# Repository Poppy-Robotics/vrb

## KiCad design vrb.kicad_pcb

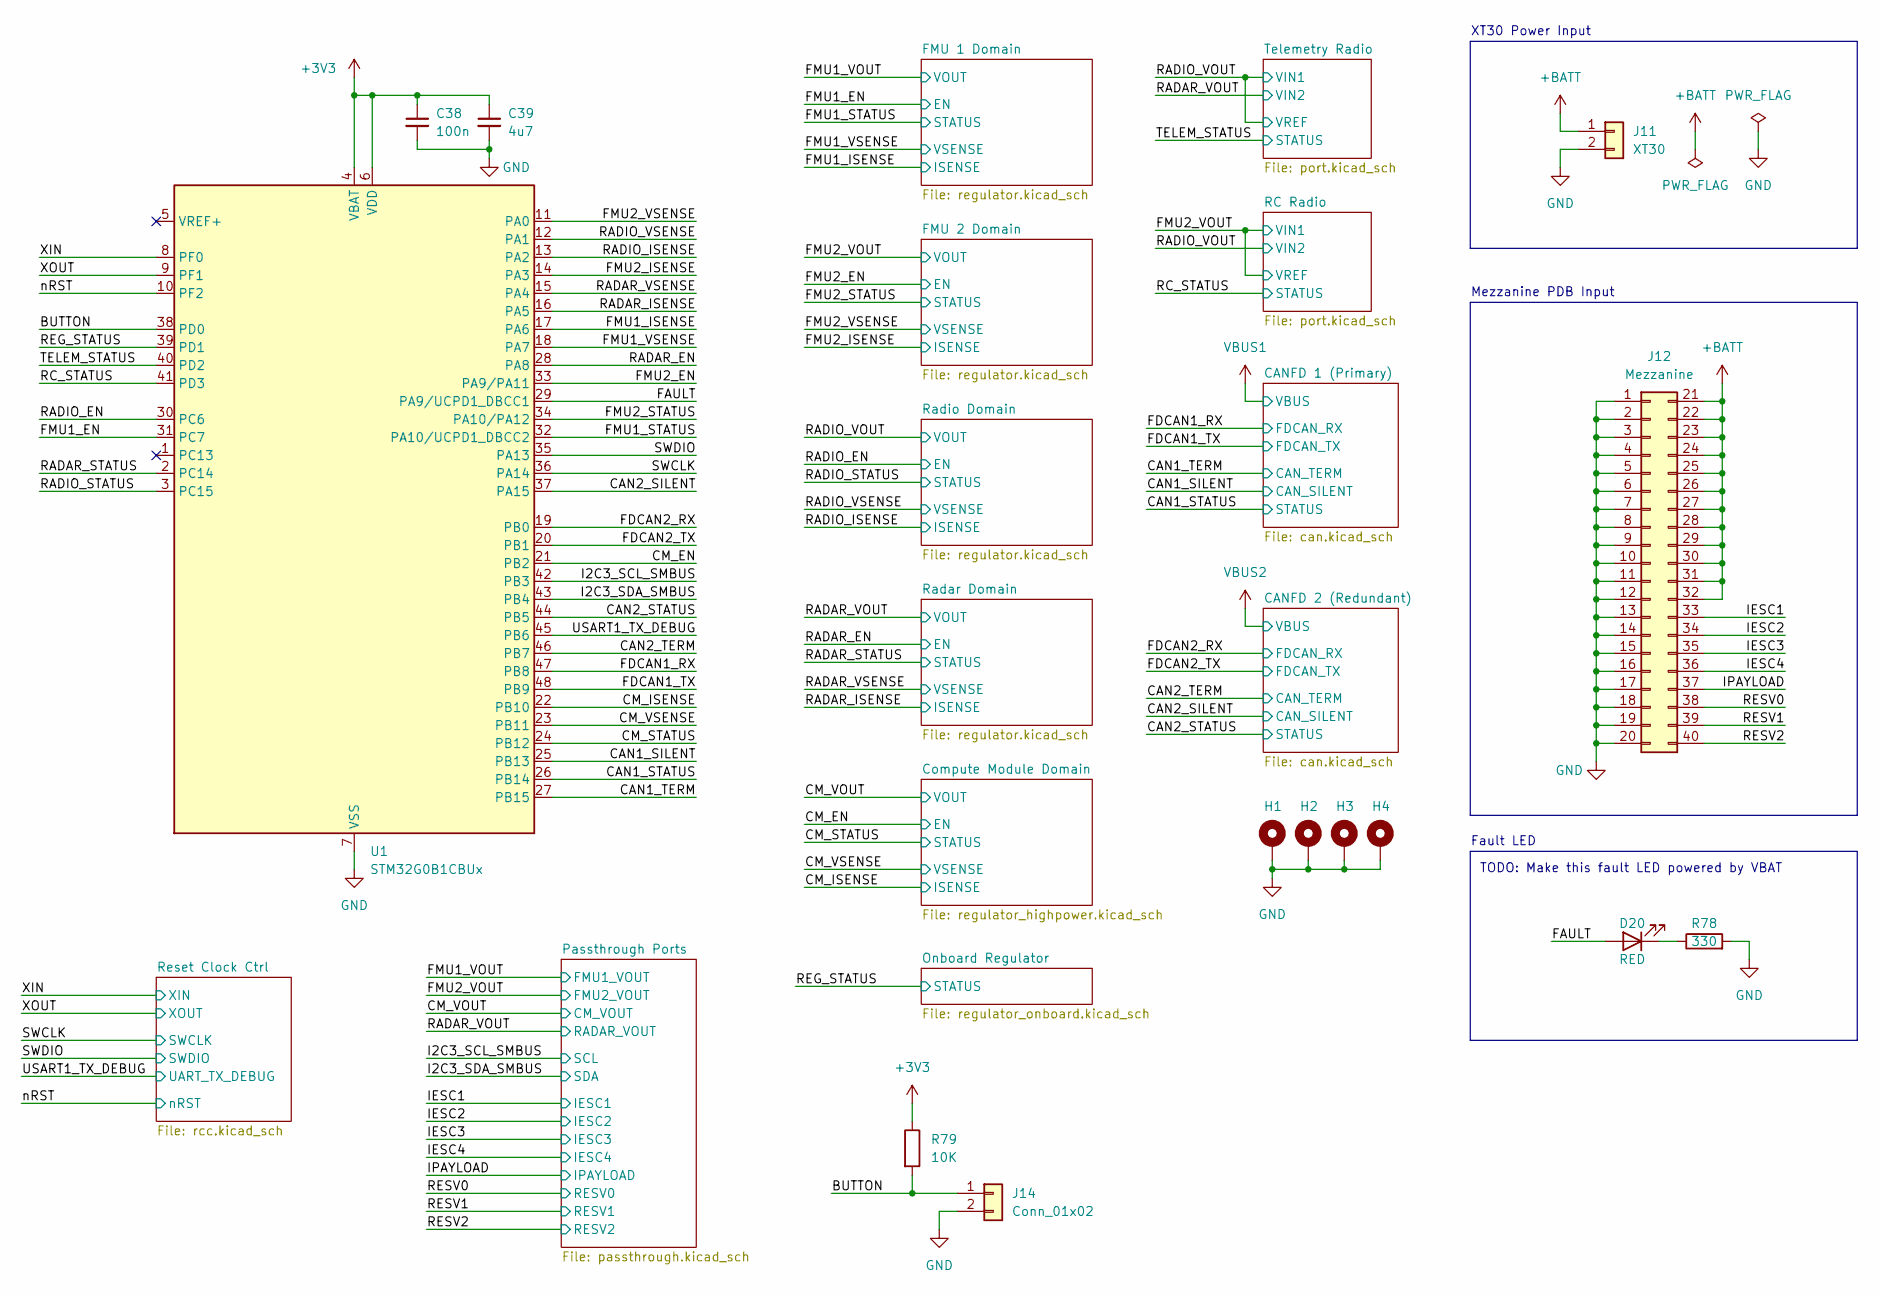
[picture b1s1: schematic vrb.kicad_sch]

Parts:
C38: 100n; C_0402_1005Metric
C39: 4u7; C_0402_1005Metric
D20: RED; LED_0603_1608Metric
H1, H2, H3, H4: MountingHole_Pad; MountingHole_3.2mm_M3_Pad_Via
J11: XT30; AMASS_XT30PW-M_1x02_P2.50mm_Horizontal
J12: Mezzanine; CON_528850474_MOL
J14: Conn_01x02; PinHeader_1x02_P2.54mm_Vertical
R78: 330; R_0402_1005Metric
R79: 10K; R_0402_1005Metric
U1: STM32G0B1CBUx; QFN-48-1EP_7x7mm_P0.5mm_EP5.6x5.6mm

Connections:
+BATT: J11.1, J12.21, J12.22, J12.23, J12.24, J12.25, J12.26, J12.27, J12.28, J12.29, J12.30, J12.31, J12.32; also elsewhere on the board
/BUTTON: J14.1, R79.2, U1.38 (PD0)
/CAN1_SILENT: U1.25 (PB13); also elsewhere on the board
/CAN1_STATUS: U1.26 (PB14); also elsewhere on the board
/CAN1_TERM: U1.27 (PB15); also elsewhere on the board
/CAN2_SILENT: U1.37 (PA15); also elsewhere on the board
/CAN2_STATUS: U1.44 (PB5); also elsewhere on the board
/CAN2_TERM: U1.46 (PB7); also elsewhere on the board
/CM_EN: U1.21 (PB2); also elsewhere on the board
/CM_ISENSE: U1.22 (PB10); also elsewhere on the board
/CM_STATUS: U1.24 (PB12); also elsewhere on the board
/CM_VSENSE: U1.23 (PB11); also elsewhere on the board
/FAULT: D20.2 (A), U1.29 (PA9/UCPD1_DBCC1)
/FDCAN1_RX: U1.47 (PB8); also elsewhere on the board
/FDCAN1_TX: U1.48 (PB9); also elsewhere on the board
/FDCAN2_RX: U1.19 (PB0); also elsewhere on the board
/FDCAN2_TX: U1.20 (PB1); also elsewhere on the board
/FMU1_EN: U1.31 (PC7); also elsewhere on the board
/FMU1_ISENSE: U1.17 (PA6); also elsewhere on the board
/FMU1_STATUS: U1.32 (PA10/UCPD1_DBCC2); also elsewhere on the board
/FMU1_VSENSE: U1.18 (PA7); also elsewhere on the board
/FMU2_EN: U1.33 (PA9/PA11); also elsewhere on the board
/FMU2_ISENSE: U1.14 (PA3); also elsewhere on the board
/FMU2_STATUS: U1.34 (PA10/PA12); also elsewhere on the board
/FMU2_VSENSE: U1.11 (PA0); also elsewhere on the board
/I2C3_SCL_SMBUS: U1.42 (PB3); also elsewhere on the board
/I2C3_SDA_SMBUS: U1.43 (PB4); also elsewhere on the board
/IESC1: J12.33; also elsewhere on the board
/IESC2: J12.34; also elsewhere on the board
/IESC3: J12.35; also elsewhere on the board
/IESC4: J12.36; also elsewhere on the board
/IPAYLOAD: J12.37; also elsewhere on the board
/RADAR_EN: U1.28 (PA8); also elsewhere on the board
/RADAR_ISENSE: U1.16 (PA5); also elsewhere on the board
/RADAR_STATUS: U1.2 (PC14); also elsewhere on the board
/RADAR_VSENSE: U1.15 (PA4); also elsewhere on the board
/RADIO_EN: U1.30 (PC6); also elsewhere on the board
/RADIO_ISENSE: U1.13 (PA2); also elsewhere on the board
/RADIO_STATUS: U1.3 (PC15); also elsewhere on the board
/RADIO_VSENSE: U1.12 (PA1); also elsewhere on the board
/RC_STATUS: U1.41 (PD3); also elsewhere on the board
/REG_STATUS: U1.39 (PD1); also elsewhere on the board
/RESV0: J12.38; also elsewhere on the board
/RESV1: J12.39; also elsewhere on the board
/RESV2: J12.40; also elsewhere on the board
/SWCLK: U1.36 (PA14); also elsewhere on the board
/SWDIO: U1.35 (PA13); also elsewhere on the board
/TELEM_STATUS: U1.40 (PD2); also elsewhere on the board
/USART1_TX_DEBUG: U1.45 (PB6); also elsewhere on the board
/XIN: U1.8 (PF0); also elsewhere on the board
/XOUT: U1.9 (PF1); also elsewhere on the board
/nRST: U1.10 (PF2); also elsewhere on the board
unnamed: D20.1 (K), R78.1

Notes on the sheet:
TODO: Make this fault LED powered by VBAT
Fault LED
XT30 Power Input
Mezzanine PDB Input

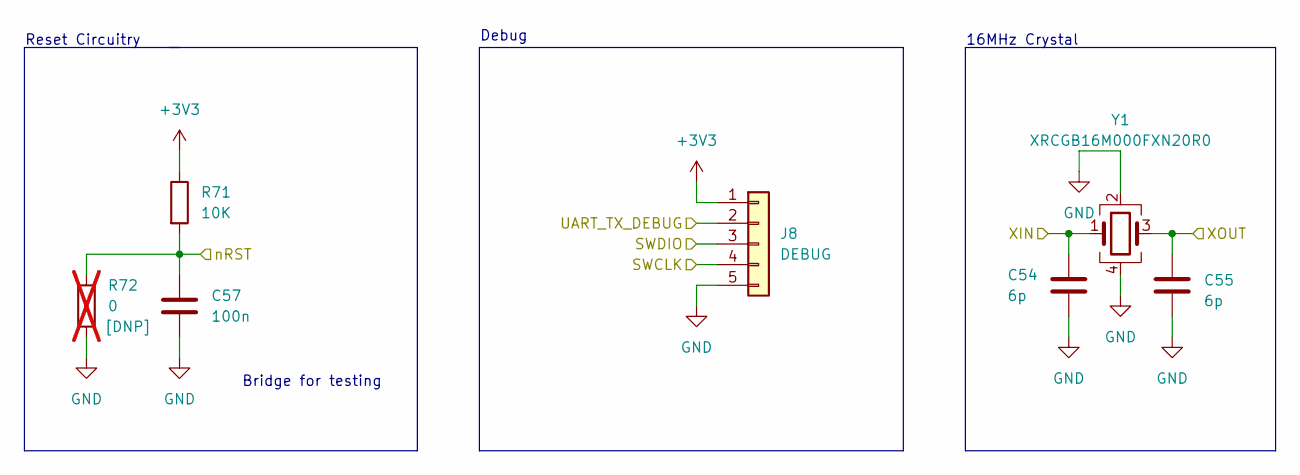
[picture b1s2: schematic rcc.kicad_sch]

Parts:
C54, C55: 6p; C_0402_1005Metric; LCSC C466231
C57: 100n; C_0402_1005Metric; LCSC C907967
J8: DEBUG; PinHeader_1x05_P2.54mm_Vertical
R71: 10K; R_0402_1005Metric; LCSC C102690
R72: 0; R_0402_1005Metric; not fitted
Y1: XRCGB16M000FXN20R0; Crystal_SMD_2016-4Pin_2.0x1.6mm; Part XRCGB16M000FXN20R0; LCSC C907977

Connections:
/SWCLK: J8.4; also elsewhere on the board
/SWDIO: J8.3; also elsewhere on the board
/USART1_TX_DEBUG: J8.2; also elsewhere on the board
/XIN: C54.1, Y1.1; also elsewhere on the board
/XOUT: C55.1, Y1.3; also elsewhere on the board
/nRST: C57.1, R71.2, R72.1; also elsewhere on the board

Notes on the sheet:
Reset Circuitry
Bridge for testing
16MHz Crystal
Debug

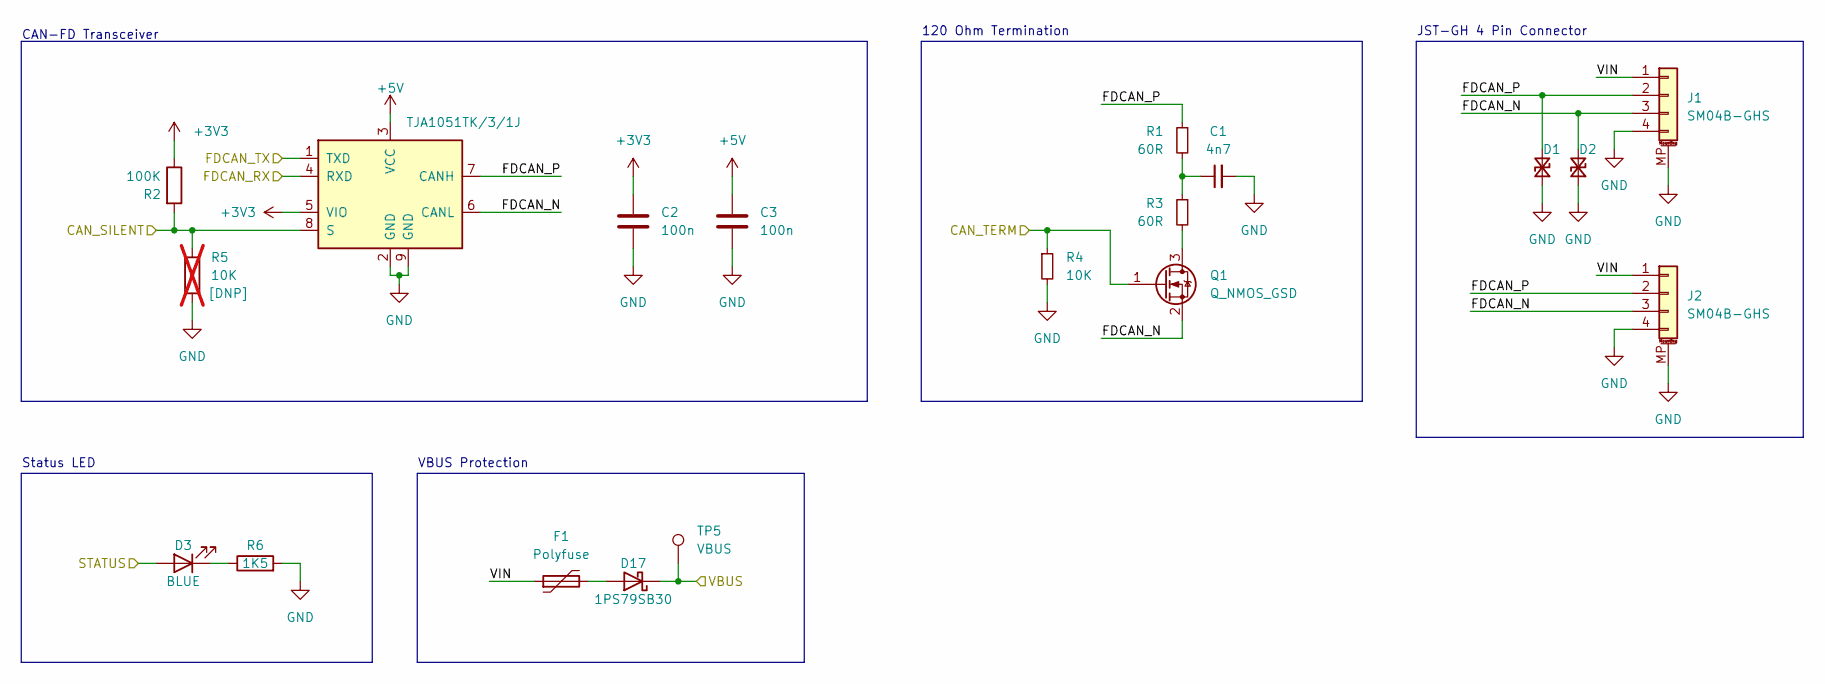
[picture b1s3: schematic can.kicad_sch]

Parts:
C1: 4n7; C_0402_1005Metric
C2, C3: 100n; C_0402_1005Metric
D1, D2: D_TVS_Small; Nexperia_DSN0603-2_0.6x0.3mm_P0.4mm
D3: BLUE; LED_0603_1608Metric
D17: 1PS79SB30; D_SOD-523; LCSC C426690
F1: Polyfuse; Fuse_1206_3216Metric
J1, J2: SM04B-GHS; JST_GH_SM04B-GHS-TB_1x04-1MP_P1.25mm_Horizontal
Q1: Q_NMOS_GSD; SOT-23-3
R1, R3: 60R; R_0402_1005Metric
R2: 100K; R_0402_1005Metric
R4: 10K; R_0402_1005Metric
R5: 10K; R_0402_1005Metric; not fitted
R6: 1K5; R_0402_1005Metric
TP5: VBUS; TestPoint_Pad_1.0x1.0mm
U2: TJA1051TK/3/1J; DFN-8-1EP_3x3mm_P0.65mm_EP1.55x2.4mm

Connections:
/CAN2_SILENT: R2.2, R5.1, U2.8 (S); also elsewhere on the board
/CAN2_STATUS: D3.2 (A); also elsewhere on the board
/CAN2_TERM: Q1.1 (G), R4.1; also elsewhere on the board
/CANFD 2 (Redundant)/FDCAN_N: D2.2 (A2), J1.3, J2.3, Q1.2 (S), U2.6 (CANL)
/CANFD 2 (Redundant)/FDCAN_P: D1.2 (A2), J1.2, J2.2, R1.1, U2.7 (CANH)
/CANFD 2 (Redundant)/VIN: F1.1, J1.1, J2.1
/FDCAN2_RX: U2.4 (RXD); also elsewhere on the board
/FDCAN2_TX: U2.1 (TXD); also elsewhere on the board
unnamed: C1.1, R1.2, R3.1
unnamed: D3.1 (K), R6.1
unnamed: D17.2 (A), F1.2
unnamed: Q1.3 (D), R3.2
VBUS2: D17.1 (K), TP5.1; also elsewhere on the board

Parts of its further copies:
C24: 4n7; C_0402_1005Metric
C25, C26: 100n; C_0402_1005Metric
D8, D9: D_TVS_Small; Nexperia_DSN0603-2_0.6x0.3mm_P0.4mm
D10: BLUE; LED_0603_1608Metric
D19: 1PS79SB30; D_SOD-523; LCSC C426690
F6: Polyfuse; Fuse_1206_3216Metric
J7, J9: SM04B-GHS; JST_GH_SM04B-GHS-TB_1x04-1MP_P1.25mm_Horizontal
Q2: Q_NMOS_GSD; SOT-23-3
R39, R41: 60R; R_0402_1005Metric
R40: 100K; R_0402_1005Metric
R45: 10K; R_0402_1005Metric
R46: 10K; R_0402_1005Metric; not fitted
R49: 1K5; R_0402_1005Metric
TP8: VBUS; TestPoint_Pad_1.0x1.0mm
U11: TJA1051TK/3/1J; DFN-8-1EP_3x3mm_P0.65mm_EP1.55x2.4mm

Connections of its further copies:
/CAN1_SILENT: R40.2, R46.1, U11.8 (S); also elsewhere on the board
/CAN1_STATUS: D10.2 (A); also elsewhere on the board
/CAN1_TERM: Q2.1 (G), R45.1; also elsewhere on the board
/CANFD 1 (Primary)/FDCAN_N: D9.2 (A2), J7.3, J9.3, Q2.2 (S), U11.6 (CANL)
/CANFD 1 (Primary)/FDCAN_P: D8.2 (A2), J7.2, J9.2, R39.1, U11.7 (CANH)
/CANFD 1 (Primary)/VIN: F6.1, J7.1, J9.1
/FDCAN1_RX: U11.4 (RXD); also elsewhere on the board
/FDCAN1_TX: U11.1 (TXD); also elsewhere on the board
unnamed: C24.1, R39.2, R41.1
unnamed: D10.1 (K), R49.1
unnamed: D19.2 (A), F6.2
unnamed: Q2.3 (D), R41.2
VBUS1: D19.1 (K), TP8.1; also elsewhere on the board

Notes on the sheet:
CAN-FD Transceiver
JST-GH 4 Pin Connector
Status LED
VBUS Protection
120 Ohm Termination

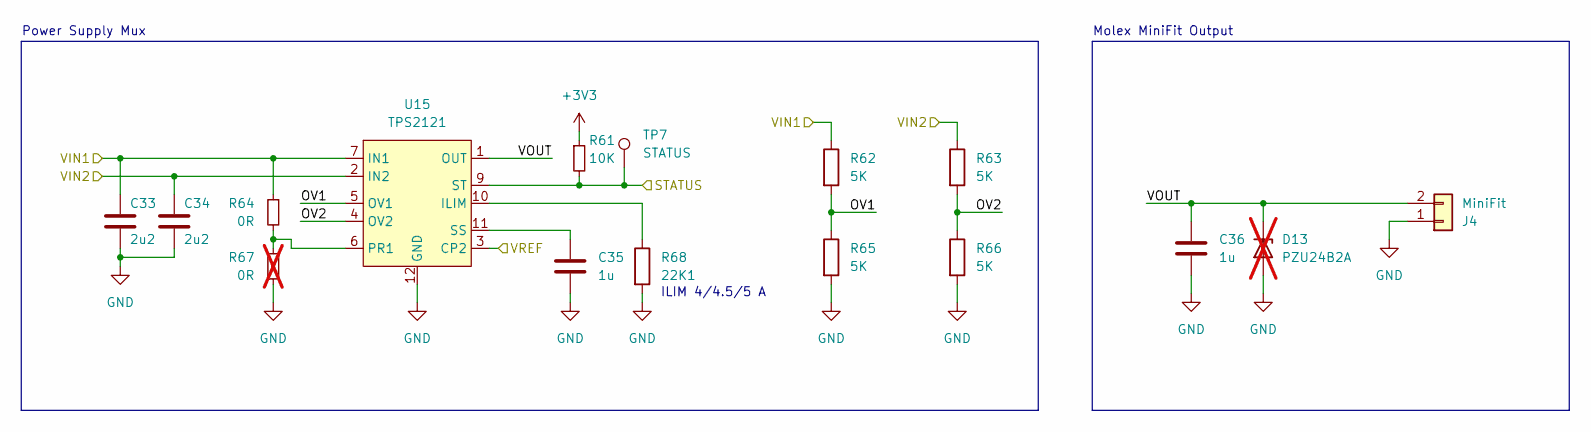
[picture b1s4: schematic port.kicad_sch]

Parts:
C33, C34: 2u2; C_0603_1608Metric
C35, C36: 1u; C_0603_1608Metric
D13: PZU24B2A; D_SOD-323F; not fitted
J4: MiniFit; Molex_Mini-Fit_Jr_5569-02A2_2x01_P4.20mm_Horizontal
R61: 10K; R_0402_1005Metric
R62, R63: 5K; R_0603_1608Metric
R64: 0R; R_0603_1608Metric
R65, R66: 5K; R_0402_1005Metric
R67: 0R; R_0402_1005Metric; not fitted
R68: 22K1; R_0603_1608Metric
TP7: STATUS; TestPoint_Pad_1.0x1.0mm
U15: TPS2121; Texas_VQFN-HR-12_2x2.5mm_P0.5mm

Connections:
/FMU2_VOUT: C33.1, R62.1, R64.1, U15.3 (CP2), U15.7 (IN1); also elsewhere on the board
/RADIO_VOUT: C34.1, R63.1, U15.2 (IN2); also elsewhere on the board
/RC Radio/OV1: R62.2, R65.1, U15.5 (OV1)
/RC Radio/OV2: R63.2, R66.1, U15.4 (OV2)
/RC Radio/VOUT: C36.1, D13.1 (K), J4.2, U15.1 (OUT), U15.8 (OUT)
/RC_STATUS: R61.2, TP7.1, U15.9 (ST); also elsewhere on the board
unnamed: R68.1, U15.10 (ILIM)
unnamed: R64.2, R67.1, U15.6 (PR1)
unnamed: C35.1, U15.11 (SS)

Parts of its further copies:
C30, C31: 2u2; C_0603_1608Metric
C32, C37: 1u; C_0603_1608Metric
D12: PZU24B2A; D_SOD-323F; not fitted
J3: MiniFit; Molex_Mini-Fit_Jr_5569-02A2_2x01_P4.20mm_Horizontal
R53: 0R; R_0402_1005Metric; not fitted
R54: 0R; R_0603_1608Metric
R55: 22K1; R_0603_1608Metric
R56: 10K; R_0402_1005Metric
R57, R60: 5K; R_0402_1005Metric
R58, R59: 5K; R_0603_1608Metric
TP6: STATUS; TestPoint_Pad_1.0x1.0mm
U14: TPS2121; Texas_VQFN-HR-12_2x2.5mm_P0.5mm

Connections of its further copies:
/RADAR_VOUT: C31.1, R59.1, U14.2 (IN2); also elsewhere on the board
/RADIO_VOUT: C30.1, R54.1, R58.1, U14.3 (CP2), U14.7 (IN1); also elsewhere on the board
/TELEM_STATUS: R56.2, TP6.1, U14.9 (ST); also elsewhere on the board
/Telemetry Radio/OV1: R57.1, R58.2, U14.5 (OV1)
/Telemetry Radio/OV2: R59.2, R60.1, U14.4 (OV2)
/Telemetry Radio/VOUT: C37.1, D12.1 (K), J3.2, U14.1 (OUT), U14.8 (OUT)
unnamed: R55.1, U14.10 (ILIM)
unnamed: R53.1, R54.2, U14.6 (PR1)
unnamed: C32.1, U14.11 (SS)

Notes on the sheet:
Molex MiniFit Output
Power Supply Mux
ILIM 4/4.5/5 A

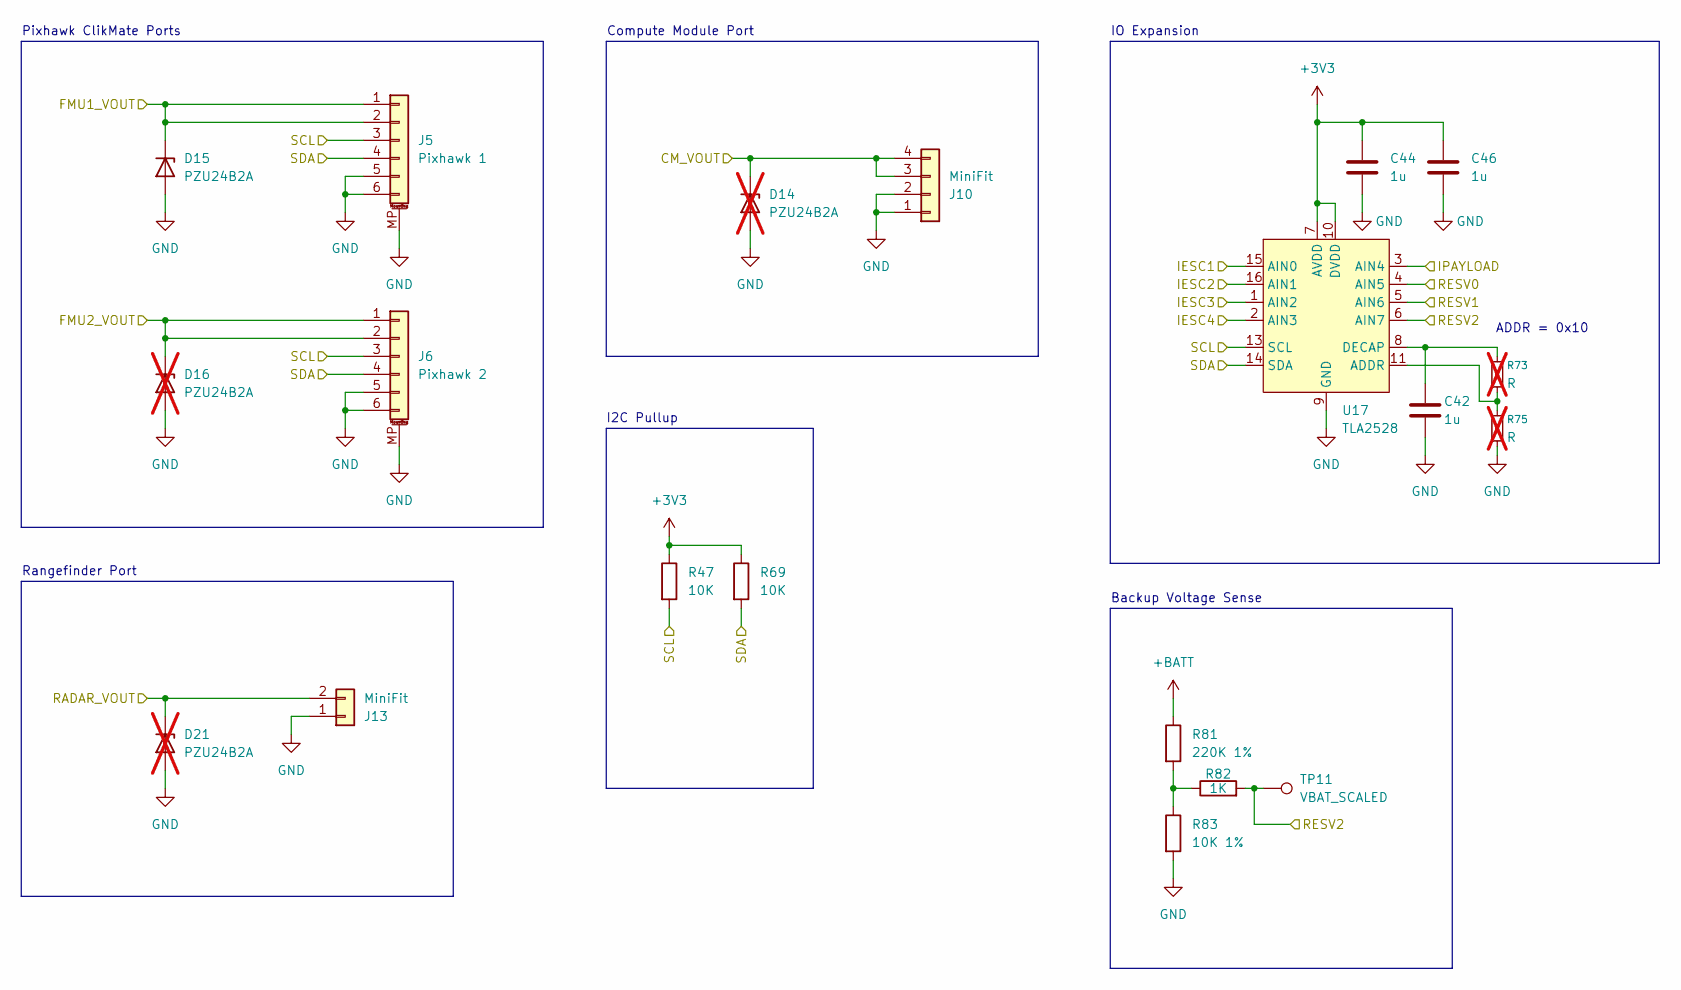
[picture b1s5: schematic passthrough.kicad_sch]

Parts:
C42, C44, C46: 1u; C_0402_1005Metric
D14, D16, D21: PZU24B2A; D_SOD-323F; not fitted
D15: PZU24B2A; D_SOD-323F
J5: Pixhawk 1; Molex_CLIK-Mate_502494-0670_1x06-1MP_P2.00mm_Horizontal
J6: Pixhawk 2; Molex_CLIK-Mate_502494-0670_1x06-1MP_P2.00mm_Horizontal
J10: MiniFit; Molex_Mini-Fit_Jr_5569-04A2_2x02_P4.20mm_Horizontal
J13: MiniFit; Molex_Mini-Fit_Jr_5569-02A2_2x01_P4.20mm_Horizontal
R47, R69: 10K; R_0402_1005Metric
R73, R75: R; R_0402_1005Metric; not fitted
R81: 220K 1%; R_0603_1608Metric
R82: 1K; R_0603_1608Metric
R83: 10K 1%; R_0603_1608Metric
TP11: VBAT_SCALED; TestPoint_Pad_1.5x1.5mm
U17: TLA2528; WQFN-16-1EP_3x3mm_P0.5mm_EP1.68x1.68mm

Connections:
+BATT: R81.1; also elsewhere on the board
/CM_VOUT: D14.1 (K), J10.3, J10.4; also elsewhere on the board
/FMU1_VOUT: D15.1 (K), J5.1, J5.2; also elsewhere on the board
/FMU2_VOUT: D16.1 (K), J6.1, J6.2; also elsewhere on the board
/I2C3_SCL_SMBUS: J5.3, J6.3, R47.2, U17.13 (SCL); also elsewhere on the board
/I2C3_SDA_SMBUS: J5.4, J6.4, R69.2, U17.14 (SDA); also elsewhere on the board
/IESC1: U17.15 (AIN0); also elsewhere on the board
/IESC2: U17.16 (AIN1); also elsewhere on the board
/IESC3: U17.1 (AIN2); also elsewhere on the board
/IESC4: U17.2 (AIN3); also elsewhere on the board
/IPAYLOAD: U17.3 (AIN4); also elsewhere on the board
/RADAR_VOUT: D21.1 (K), J13.2; also elsewhere on the board
/RESV0: U17.4 (AIN5); also elsewhere on the board
/RESV1: U17.5 (AIN6); also elsewhere on the board
/RESV2: R82.2, TP11.1, U17.6 (AIN7); also elsewhere on the board
unnamed: R81.2, R82.1, R83.1
unnamed: R73.2, R75.1, U17.11 (ADDR)
unnamed: C42.1, R73.1, U17.8 (DECAP)

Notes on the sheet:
Pixhawk ClikMate Ports
I2C Pullup
Rangefinder Port
Backup Voltage Sense
ADDR = 0x10
Compute Module Port
IO Expansion

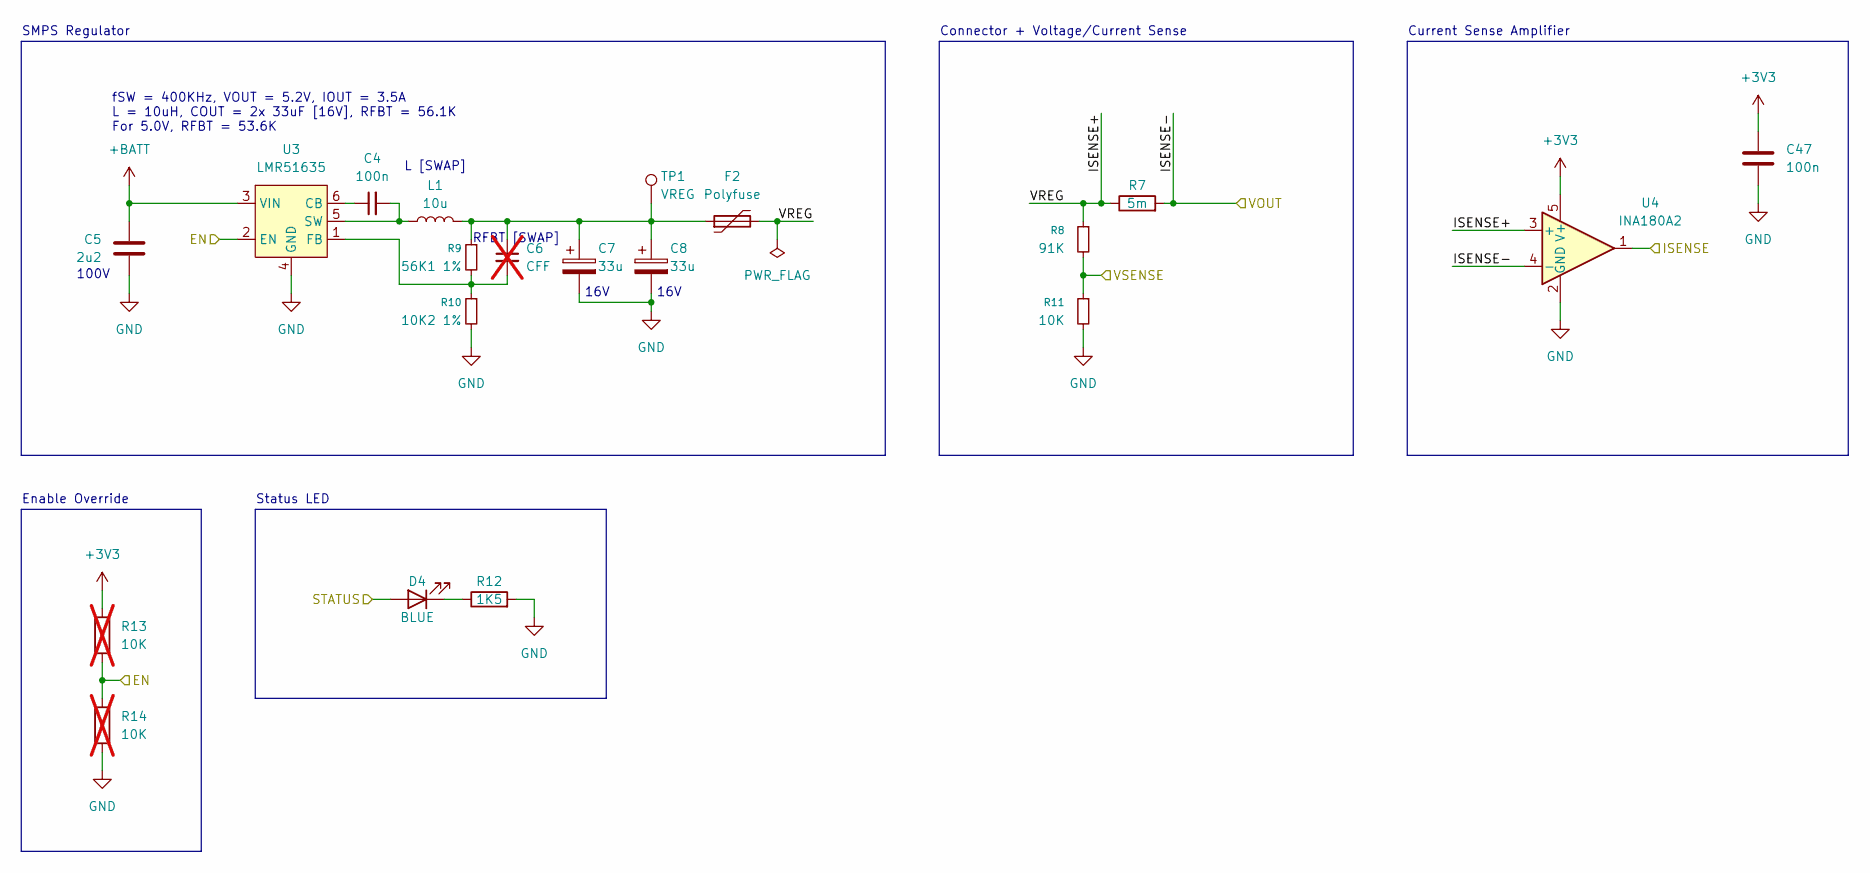
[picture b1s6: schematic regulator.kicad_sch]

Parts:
C4: 100n; C_0805_2012Metric
C5: 2u2; C_1206_3216Metric
C6: CFF; C_0805_2012Metric; not fitted
C7, C8: 33u; CP_EIA-3528-12_Kemet-T
C47: 100n; C_0402_1005Metric
D4: BLUE; LED_0603_1608Metric
F2: Polyfuse; Fuse_1206_3216Metric
L1: 10u; L_Bourns_SRP7028A_7.3x6.6mm
R7: 5m; R_1206_3216Metric
R8: 91K; R_0402_1005Metric
R9: 56K1 1%; R_0603_1608Metric
R10: 10K2 1%; R_0603_1608Metric
R11: 10K; R_0402_1005Metric
R12: 1K5; R_0402_1005Metric
R13, R14: 10K; R_0603_1608Metric; not fitted
TP1: VREG; TestPoint_Pad_2.0x2.0mm
U3: LMR51635; SOT-23-6
U4: INA180A2; SOT-23-5

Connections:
+BATT: C5.1, U3.3 (VIN); also elsewhere on the board
/FMU1_EN: R13.2, R14.1, U3.2 (EN); also elsewhere on the board
/FMU1_ISENSE: U4.1; also elsewhere on the board
/FMU1_STATUS: D4.2 (A); also elsewhere on the board
/FMU1_VOUT: R7.2, U4.4 (-); also elsewhere on the board
/FMU1_VSENSE: R8.2, R11.1; also elsewhere on the board
/FMU 1 Domain/ISENSE+: F2.2, R7.1, R8.1, U4.3 (+)
unnamed: C6.1, C7.1, C8.1, F2.1, L1.2, R9.1, TP1.1
unnamed: D4.1 (K), R12.1
unnamed: C4.1, U3.6 (CB)
unnamed: C6.2, R9.2, R10.1, U3.1 (FB)
unnamed: C4.2, L1.1, U3.5 (SW)

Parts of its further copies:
C9, C14, C19: 100n; C_0805_2012Metric
C10, C15, C20: 2u2; C_1206_3216Metric
C11, C16, C21: CFF; C_0805_2012Metric; not fitted
C12, C13, C17, C18, C22, C23: 33u; CP_EIA-3528-12_Kemet-T
C48, C49, C50: 100n; C_0402_1005Metric
D5, D6, D7: BLUE; LED_0603_1608Metric
F3, F4, F5: Polyfuse; Fuse_1206_3216Metric
L2, L3, L4: 10u; L_Bourns_SRP7028A_7.3x6.6mm
R15, R23, R31: 5m; R_1206_3216Metric
R16, R24, R32: 91K; R_0402_1005Metric
R17, R25, R33: 56K1 1%; R_0603_1608Metric
R18, R26, R34: 10K2 1%; R_0603_1608Metric
R19, R27, R35: 10K; R_0402_1005Metric
R20, R28, R36: 1K5; R_0402_1005Metric
R21, R22, R29, R30, R37, R38: 10K; R_0603_1608Metric; not fitted
TP2, TP3, TP4: VREG; TestPoint_Pad_2.0x2.0mm
U5, U7, U9: LMR51635; SOT-23-6
U6, U8, U10: INA180A2; SOT-23-5

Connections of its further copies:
+BATT: C10.1, C15.1, C20.1, U5.3 (VIN), U7.3 (VIN), U9.3 (VIN); also elsewhere on the board
/FMU2_EN: R21.2, R22.1, U5.2 (EN); also elsewhere on the board
/FMU2_ISENSE: U6.1; also elsewhere on the board
/FMU2_STATUS: D5.2 (A); also elsewhere on the board
/FMU2_VOUT: R15.2, U6.4 (-); also elsewhere on the board
/FMU2_VSENSE: R16.2, R19.1; also elsewhere on the board
/FMU 2 Domain/ISENSE+: F3.2, R15.1, R16.1, U6.3 (+)
/RADAR_EN: R37.2, R38.1, U9.2 (EN); also elsewhere on the board
/RADAR_ISENSE: U10.1; also elsewhere on the board
/RADAR_STATUS: D7.2 (A); also elsewhere on the board
/RADAR_VOUT: R31.2, U10.4 (-); also elsewhere on the board
/RADAR_VSENSE: R32.2, R35.1; also elsewhere on the board
/RADIO_EN: R29.2, R30.1, U7.2 (EN); also elsewhere on the board
/RADIO_ISENSE: U8.1; also elsewhere on the board
/RADIO_STATUS: D6.2 (A); also elsewhere on the board
/RADIO_VOUT: R23.2, U8.4 (-); also elsewhere on the board
/RADIO_VSENSE: R24.2, R27.1; also elsewhere on the board
/Radar Domain/ISENSE+: F5.2, R31.1, R32.1, U10.3 (+)
/Radio Domain/ISENSE+: F4.2, R23.1, R24.1, U8.3 (+)
unnamed: C11.1, C12.1, C13.1, F3.1, L2.2, R17.1, TP2.1
unnamed: C16.1, C17.1, C18.1, F4.1, L3.2, R25.1, TP3.1
unnamed: C21.1, C22.1, C23.1, F5.1, L4.2, R33.1, TP4.1
unnamed: D5.1 (K), R20.1
unnamed: D6.1 (K), R28.1
unnamed: D7.1 (K), R36.1
unnamed: C9.1, U5.6 (CB)
unnamed: C11.2, R17.2, R18.1, U5.1 (FB)
unnamed: C9.2, L2.1, U5.5 (SW)
unnamed: C14.1, U7.6 (CB)
unnamed: C16.2, R25.2, R26.1, U7.1 (FB)
unnamed: C14.2, L3.1, U7.5 (SW)
unnamed: C19.1, U9.6 (CB)
unnamed: C21.2, R33.2, R34.1, U9.1 (FB)
unnamed: C19.2, L4.1, U9.5 (SW)

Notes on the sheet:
Enable Override
16V
Status LED
Current Sense Amplifier
L [SWAP]
RFBT [SWAP]
SMPS Regulator
Connector + Voltage/Current Sense
fSW = 400KHz, VOUT = 5.2V, IOUT = 3.5A L = 10uH, COUT = 2x 33uF [16V], RFBT = 56.1K For 5.0V, RFBT = 53.6K
100V

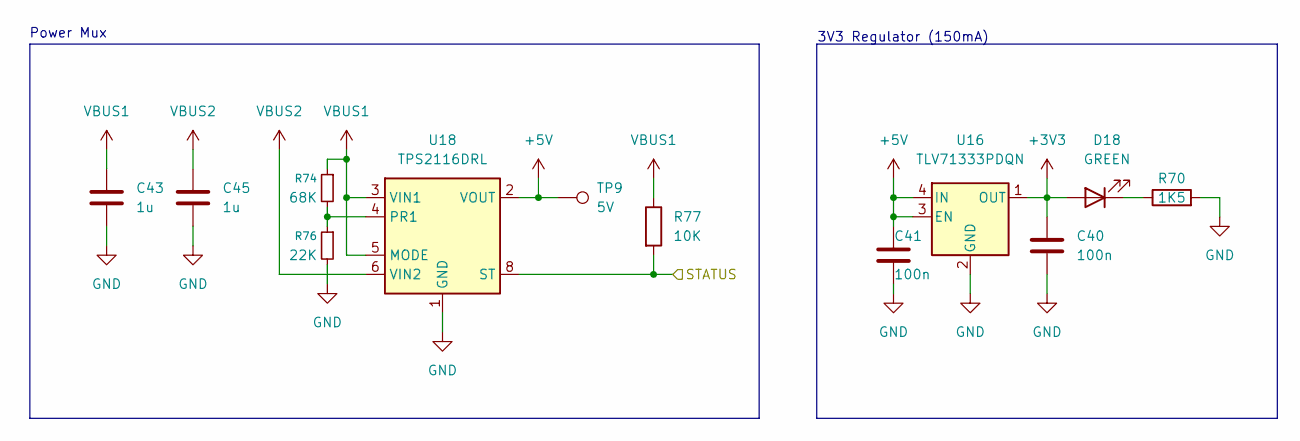
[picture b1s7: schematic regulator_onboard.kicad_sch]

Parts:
C40, C41: 100n; C_0603_1608Metric; LCSC C282519
C43, C45: 1u; C_0603_1608Metric
D18: GREEN; LED_0603_1608Metric; Part QBLP595-IG; LCSC C2856703
R70: 1K5; R_0402_1005Metric; LCSC C25930
R74: 68K; R_0402_1005Metric
R76: 22K; R_0402_1005Metric
R77: 10K; R_0402_1005Metric
TP9: 5V; TestPoint_Pad_1.0x1.0mm
U16: TLV71333PDQN; SOT-23-5; LCSC C2867340
U18: TPS2116DRL; SOT-583-8

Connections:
/REG_STATUS: R77.2, U18.8 (ST); also elsewhere on the board
unnamed: D18.1 (K), R70.1
unnamed: R74.2, R76.1, U18.4 (PR1)
VBUS1: C43.1, R74.1, R77.1, U18.3 (VIN1), U18.5 (MODE); also elsewhere on the board
VBUS2: C45.1, U18.6 (VIN2); also elsewhere on the board

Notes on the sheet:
3V3 Regulator (150mA)
Power Mux

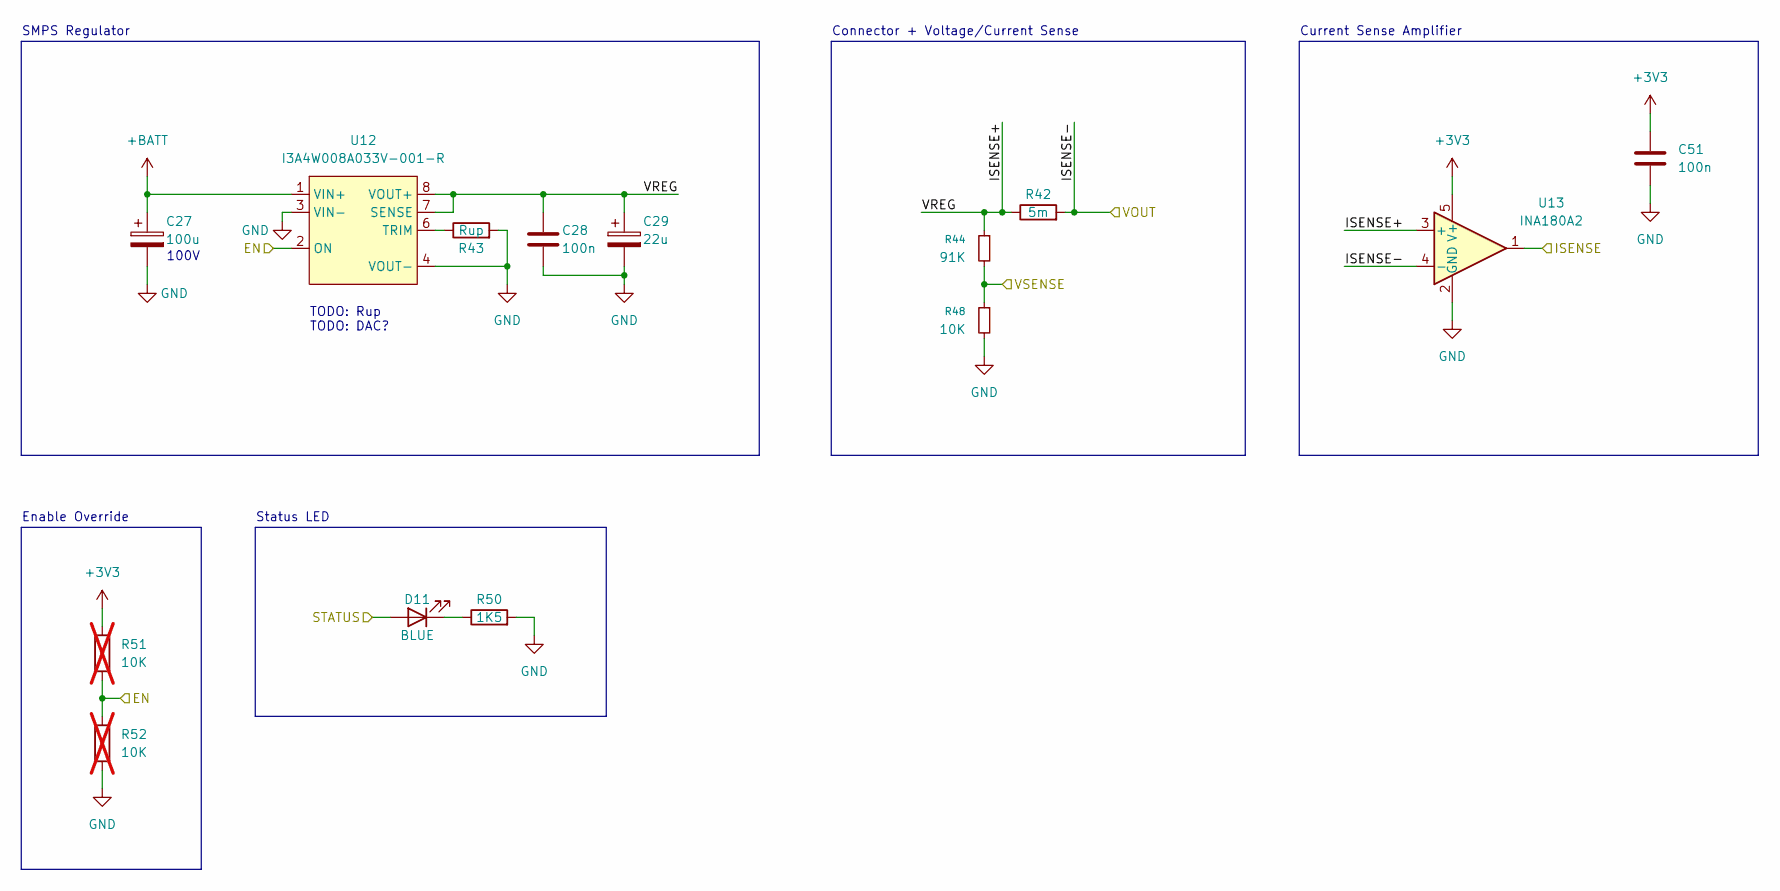
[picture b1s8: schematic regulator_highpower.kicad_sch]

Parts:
C27: 100u; C_1206_3216Metric
C28: 100n; C_0805_2012Metric
C29: 22u; C_0805_2012Metric
C51: 100n; C_0402_1005Metric
D11: BLUE; LED_0603_1608Metric
R42: 5m; R_1206_3216Metric
R43: Rup; R_0603_1608Metric
R44: 91K; R_0402_1005Metric
R48: 10K; R_0603_1608Metric
R50: 1K5; R_0402_1005Metric
R51, R52: 10K; R_0603_1608Metric; not fitted
U12: I3A4W008A033V-001-R; CONV_I3A4W008A033V-001-R
U13: INA180A2; SOT-23-5

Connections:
+BATT: C27.1, U12.1 (VIN+); also elsewhere on the board
/CM_EN: R51.2, R52.1, U12.2 (ON); also elsewhere on the board
/CM_ISENSE: U13.1; also elsewhere on the board
/CM_STATUS: D11.2 (A); also elsewhere on the board
/CM_VOUT: R42.2, U13.4 (-); also elsewhere on the board
/CM_VSENSE: R44.2, R48.1; also elsewhere on the board
/Compute Module Domain/ISENSE+: C28.1, C29.1, R42.1, R44.1, U12.7 (SENSE), U12.8 (VOUT+), U13.3 (+)
unnamed: D11.1 (K), R50.1
unnamed: R43.1, U12.6 (TRIM)

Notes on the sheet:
Enable Override
SMPS Regulator
Current Sense Amplifier
TODO: Rup TODO: DAC?
Status LED
Connector + Voltage/Current Sense
100V

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
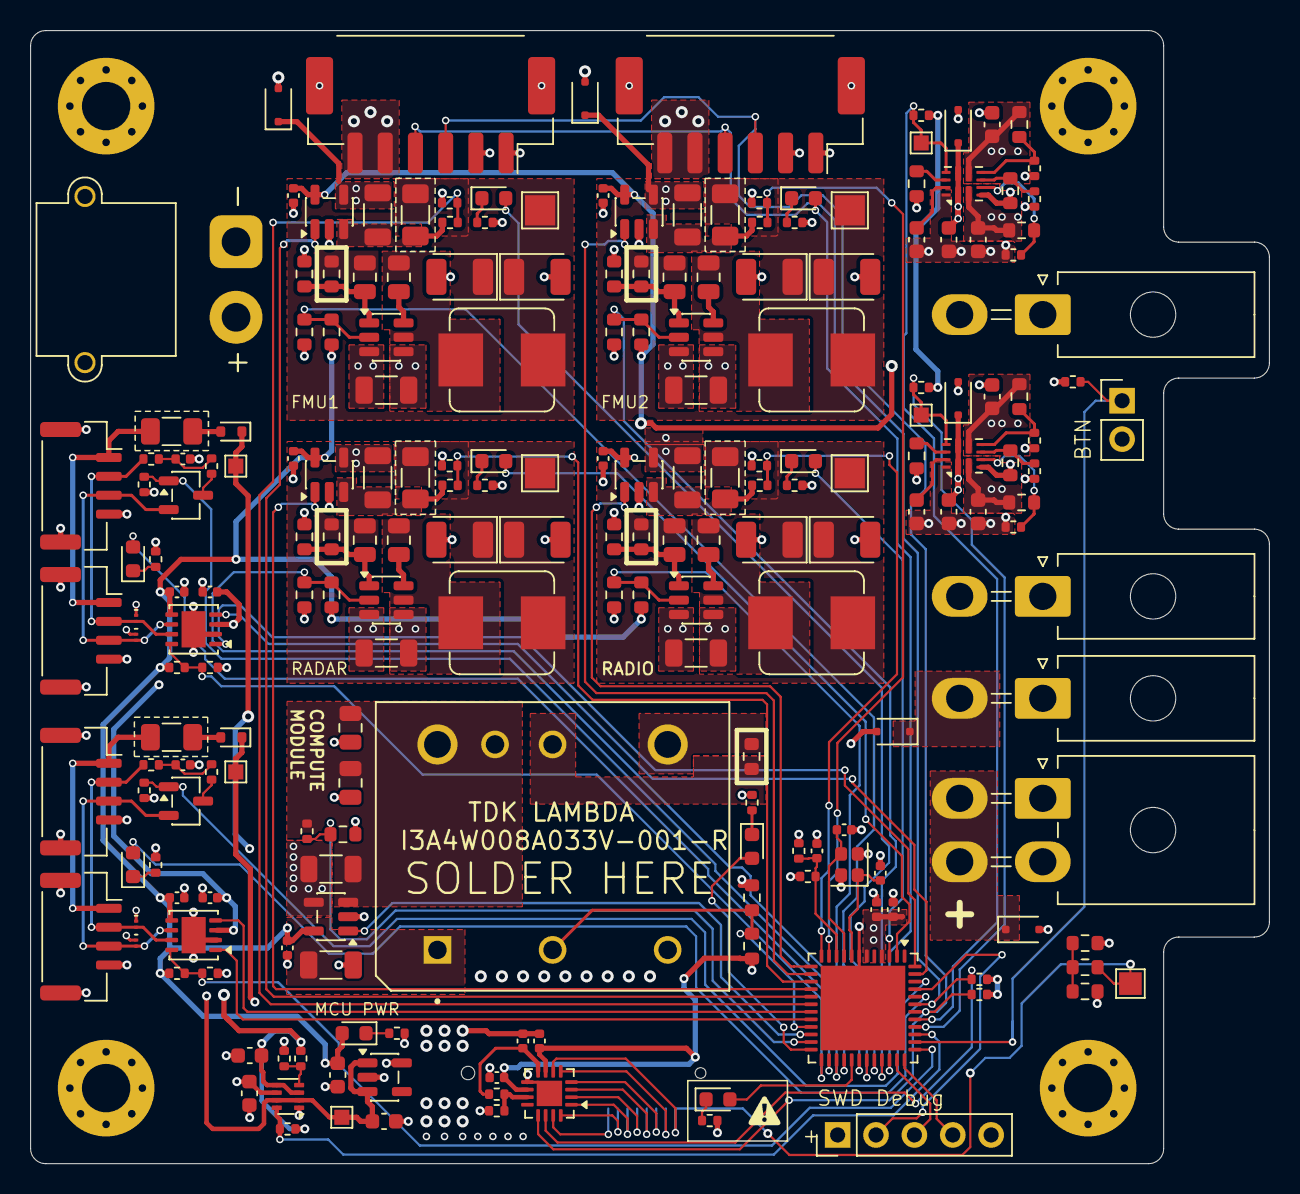
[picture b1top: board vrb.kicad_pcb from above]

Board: 6 copper layers, 82.0 x 75.0 mm, 216 parts (1 on the bottom side), 121 nets.

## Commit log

2025-12-29 nearly done with layout
2025-12-30 update standard libs
2025-12-30 more layout work
2026-01-09 fix capacitor sizes, clean up silkscreen, export
2026-01-10 minor revisions
